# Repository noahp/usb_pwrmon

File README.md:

usb_pwrmon
=====
Simple usb port current/voltage measurement with display.

render
=====

oled breakout
=====

comp info
=====

oled
-----
http://www.aliexpress.com/snapshot/276751791.html
http://rusticengineering.com/2010/05/10/oled-0-96-breakout-board-sh1101a-driver/

micro
-----
freescale ksz24/25/26  
http://cache.freescale.com/files/32bit/doc/data_sheet/KL02P32M48SF0.pdf  
http://cache.freescale.com/files/32bit/doc/ref_manual/KL02P32M48SF0RM.pdf

sns resist:
-----
http://www.mouser.com/ProductDetail/Ohmite/LVK12R010DER/?qs=sGAEpiMZZMtlleCFQhR%2fzSLc77HVEnhv2DNaRf6lglA%3d

opamp:
-----
current sense, fixed at 80 gain:
http://www.mouser.com/ProductDetail/Analog-Devices/AD8293G80ARJZ-R7/?qs=sGAEpiMZZMvEn2pkGav3bNYdL9E%2foSzJYdqf7Uk6kdc%3d
that's a range of 0-4.125A with a shunt resistor of 0.010 Ohms. assuming 16-bit adc (on freescale kl25), ~15 bits per mA.

button:
-----
http://www.mouser.com/Search/ProductDetail.aspx?R=1571621-1virtualkey50660000virtualkey506-1571621-1

usb connectors
-----
[Male A](http://www.mouser.com/ProductDetail/Keystone-Electronics/931/?qs=sGAEpiMZZMulM8LPOQ%252byk63mhAufmuInYp1ViSdVrzg%3d)  
[Female A](http://www.mouser.com/ProductDetail/Amphenol-Commercial-Products/UE27AC5410H/?qs=sGAEpiMZZMulM8LPOQ%252byk4r5VEz1yZV2Iljm%2fKqttNs%3d)  
[Micro B](http://www.mouser.com/ProductDetail/FCI/10118192-0001LF/?qs=sGAEpiMZZMulM8LPOQ%252byk2%252bTbV8%2f2X5vivRX5xKgOBI%3d)

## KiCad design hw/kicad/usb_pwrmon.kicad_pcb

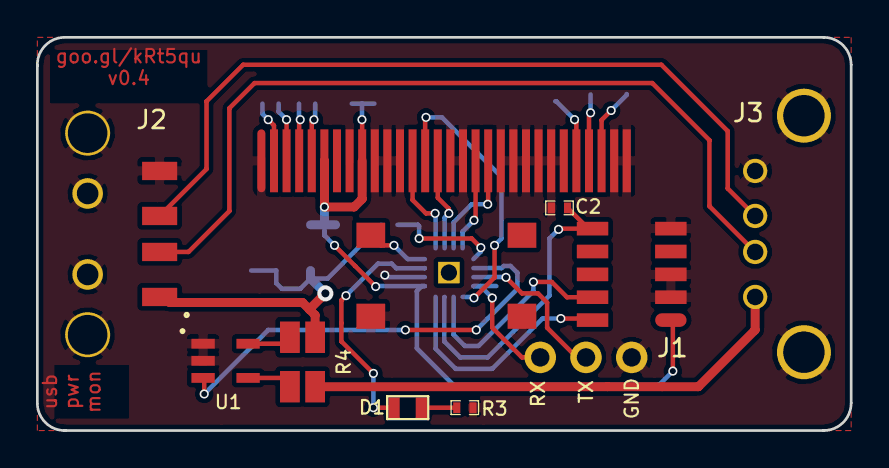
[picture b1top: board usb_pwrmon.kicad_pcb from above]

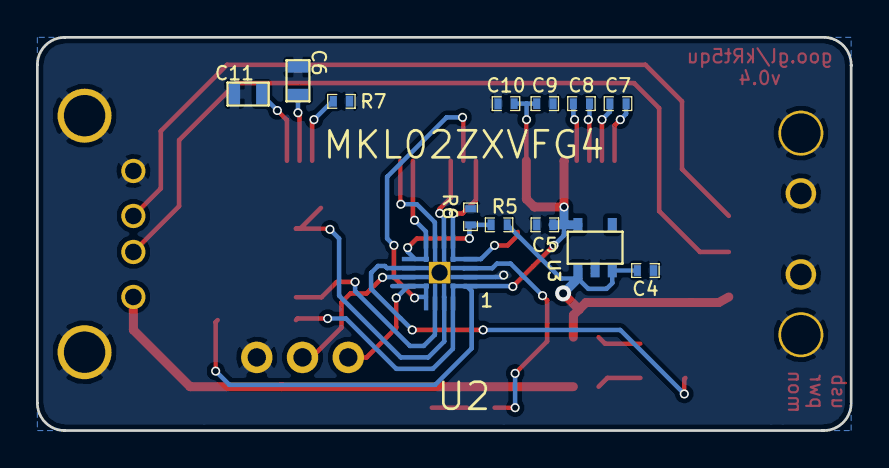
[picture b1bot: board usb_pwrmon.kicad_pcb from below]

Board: 2 copper layers, 45.2 x 21.8 mm, 26 parts (13 on the bottom side), 28 nets.

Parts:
C2: 0.1uF; SM0402
C4, C5, C7, C8, C9, C10: 1uF; SM0402
C6: 2.2uF/16V; SM0603
C11: 10uF; SM0603
D1: LED; SM0603
J1: ARM_10PIN; ARM_10_PIN_SMT
J2: USB_MALE_A; usb_a_male_M701-280442
J3: USB_FEMALE_A; usb_female_a
J_1: OLED_FPC_CONN; oled_fpc_30
P1: TX; TEST_0.100
P2: RX; TEST_0.100
P3: GND; TEST_0.100
R3: 330R; SM0402
R4: LVK12-SHUNT; lvk12
R5, R6: 25K; SM0402
R7: 390K; SM0402
SW1: SW_PUSH; spst_pushbutton_smd
U1: MAX9938; sot23-5_noah
U2: MKL02ZXVFG4; MKL02_QFN16
U3: AAT3221; SOT23-5

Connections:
+3.3v: C5.1, C9.2, C10.2, J1.1, J_1.6, J_1.9, U2.1, U3.5
ADC_OUT: U1.3, U2.10
GND: C2.2, C4.2, C5.2, C6.1, C9.1, C10.1, C11.1, J1.3, J1.5, J1.9, J2.4, J2.5, J3.4, J3.5, J_1.1, J_1.8, J_1.10, J_1.11, J_1.12, J_1.16, J_1.17, J_1.20, J_1.21, J_1.22, J_1.23, J_1.24, J_1.25, J_1.29, J_1.30, P3.1, R3.2, R6.2, R7.1, SW1.1, U1.1, U1.2, U2.2, U3.2
unnamed: D1.2, R3.1
unnamed: D1.1, U2.3
unnamed: J3.1, R4.3, R4.4, U1.4
unnamed: C8.1, J_1.5
unnamed: C7.1, J_1.3
unnamed: C8.2, J_1.4
unnamed: C7.2, J_1.2
unnamed: C11.2, J_1.28
unnamed: C6.2, J_1.27
unnamed: J_1.26, R7.2
NRESET: C2.1, J1.10, U2.15
OLED_D0/SPI_SCLK/I2C_SCK: J_1.18, U2.8
OLED_D1/SPI_SDIN/I2C_SDA: J_1.19, U2.7
OLED_DC/I2X_SA0: J_1.15, U2.6
OLED_~CS: J_1.13, U2.5
OLED_~RST: J_1.14, U2.13
SERIAL_RX: P2.1, U2.12
SERIAL_TX: P1.1, U2.11
SWCLK: J1.4, U2.14
SWDIO: J1.2, U2.16
SW_SNS: SW1.2, U2.4
USB_DM: J2.3, J3.3
USB_DP: J2.2, J3.2
USB_VBUS: C4.1, J2.1, R4.1, R4.2, R5.1, U1.5, U3.1, U3.3
VBUS_SENSE: R5.2, R6.1, U2.9

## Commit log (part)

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2013-01-23 - add basic kicad project & blank schematic
2013-01-23 - add pic & lcd panel components
2013-02-22 - add usb ports (will be m/f footprints later).
2013-02-23 - few more pins.
2013-02-23 - add pushbutton for wakeup (portb) and control
2013-02-23 - add ftdi, add decouples for ic vpp
2013-02-25 - rename usb connectors
2013-03-11 - update to low-side current sense. i think this is about done.
2013-06-25 - add kicadlib submodule
2013-08-04 - add cmp file
2013-08-04 - remove everything except one op-amp
2013-10-09 - add oled display docs
    Former-commit-id: 7fdf5cce20b69188c61fdde9001fc521c2195e7e
2013-10-09 - add oled display docs
2013-10-11 save
2013-10-11 - remove submodule?
2013-10-11 add lib
2013-10-11 remove old format pcb
2013-10-11 pcb renders
2013-10-29 Update README.md
    Former-commit-id: 70bd3ad641af45a11b6eda4deac7096167ec7fa2 [formerly 70bd3ad641af45a11b6eda4deac7096167ec7fa2 [formerly 16fa63f3193e395ecc1da543856f4a60976ed051]]
    Former-commit-id: 736f9969bc4425ab0775a6e428a168e7dd024f6e
    Former-commit-id: 912d237d8af61a4f4f4660b6a735a109fcdfcc66
2013-10-29 Update README.md
    Former-commit-id: 6964e2daf4fc5f64c7605d358488f3e401891eeb
2013-10-29 Update README.md
    Former-commit-id: b29b2106ccbbed165739fa0c228b58bd4ef09a9a
2013-10-30 Update README.md
    Former-commit-id: b8099f7d58f96c51709ed39b64d6d2cdd5e7d5e7 [formerly b8099f7d58f96c51709ed39b64d6d2cdd5e7d5e7 [formerly c15122072ee5d19dd1f13ced2584c3b0514e7588]]
    Former-commit-id: cf23cb98488d09c327cf99636e96615ef90f1e47
    Former-commit-id: be61c741d09226cad19315a5aa11420df0aa2ce2
2013-10-31 remove ref files
    Former-commit-id: 517aac4d8dee8b040f95a6394ec9b84ba33d6f9b
2013-10-31 remove gerbers
    Former-commit-id: 32eedcece8f8c7c22dcb1d825b03550649e028e7
2013-10-31 add old gerbers to subfolder
    Former-commit-id: 506f4019bd9ce86fdc2229ec208849322aa528c9 [formerly 506f4019bd9ce86fdc2229ec208849322aa528c9 [formerly 5891018200ce89c8d6c42409d1824482201694f4]]
    Former-commit-id: d5a737b1643705d074663e591d51fc8108181a90
    Former-commit-id: 41f91e4560a02bc82f3c82b34b4f3513ce68339e
2013-10-31 add old gerbers to subfolder
    Former-commit-id: 5891018200ce89c8d6c42409d1824482201694f4
2013-10-31 update kicadlib
2013-10-31 new schematic with mkl24/5 and ad8293g80 amp
    Former-commit-id: ac4693991d8abdc5d445cbaefc909b446d0d6420 [formerly ac4693991d8abdc5d445cbaefc909b446d0d6420 [formerly 4a9109472a9407fe635b43a95cd1c65a3b81beb9]]
    Former-commit-id: 1dbed20921111c72b593823ada45a3dbf7315b21
    Former-commit-id: 6b7cd41b20ec488c91ded0642a15e9776eb08592
2013-10-31 working on sch
    Former-commit-id: f8ac0ea2000f7e923b448f6217d0ea35cba610c7 [formerly f8ac0ea2000f7e923b448f6217d0ea35cba610c7 [formerly 29f02dbf4e773d56ffa3c3261b2d66c1b951bd1d]]
    Former-commit-id: c5269c944eb81a72d4da92abec835d3a79df764e
    Former-commit-id: 3b6b85954bec87b50fb528209276810c0470e93d
2013-10-31 pop arm debug header
    Former-commit-id: d5df85ed5a434d3ef5b0c7d2dfbc2d922e464fb3 [formerly d5df85ed5a434d3ef5b0c7d2dfbc2d922e464fb3 [formerly f2c820a7cda0a871eab099a68b0b6fad4a23c513]]
    Former-commit-id: 8dfd089300d51ac9194a1659276579516a26efa6
    Former-commit-id: 3cafe83c497ca93ebd9511251291f78c0a64231a
2013-10-31 pop arm debug header
    Former-commit-id: f2c820a7cda0a871eab099a68b0b6fad4a23c513
2013-11-07 Update README.md
    Former-commit-id: 541ae88adf55100f2ead3d13b665923feb6b35fc [formerly 541ae88adf55100f2ead3d13b665923feb6b35fc [formerly 3313f8d4bca9e39602681fdedcab0baa98b72fa6]]
    Former-commit-id: 9264d39825ae36b9c403045ea3fb9e9853812328
    Former-commit-id: 19a171e3758995f70dade9d33aa752f5fdaea0d5
2013-11-09 - fpc connector
    Former-commit-id: 6685d56f5c7f47c431a70211aba2797cf116a25f [formerly 6685d56f5c7f47c431a70211aba2797cf116a25f [formerly 39fcca6794e6a0a2376122315f6af96ae3c01e4f]]
    Former-commit-id: 3bfaab40e79fdfb916e4c6f7b2db3d4696864c31
    Former-commit-id: dbef93559065cb2be07040512478b7806f2621b6
2013-11-10 - add passives and some connections
    Former-commit-id: 0cbe066add0483a1fb74efe12cbe9abbbee8238b [formerly 0cbe066add0483a1fb74efe12cbe9abbbee8238b [formerly 632aac8206b8db47b8f5b2e04e83e7b3be4b6b11]]
    Former-commit-id: a0e75f49b152e5eca435386ea37dbbfa80a0be74
    Former-commit-id: fe0be35bf74c2a8adf19254a67f5b87cb48fbc1c
2013-11-10 - add passives and some connections
    Former-commit-id: 632aac8206b8db47b8f5b2e04e83e7b3be4b6b11
2013-11-10 sch done
    Former-commit-id: 4d012d6b3e56cf83ea9f75bc49d9e1903af969ce
2013-11-10 - start work on pcb
    Former-commit-id: e6562ca754a2c3bdfaa1edcaa4f370bf0480df17
2013-11-13 - some work on pcb
2013-11-13 layout done
2013-11-13 as ordered
    Former-commit-id: 723d12aa2e927baf709e922beb68eb4c6786b970 [formerly 723d12aa2e927baf709e922beb68eb4c6786b970 [formerly 3f4dc9afe7143e35ff6037357ae27188abc31b63]]
    Former-commit-id: a81fd3ca1cf09aa850dd447895322da6a8cd5efa
    Former-commit-id: 210a18c5bd8d0dae89b912255909798f745396fd
2013-11-13 as ordered
2013-11-13 add pcb images
    Former-commit-id: ef8c1a849b213638d83b8e597bf651b582da5368
2013-11-13 Update README.md
    Former-commit-id: 6bb333fa8edbaf539f8ec23fd432706c74fe40d2 [formerly 6bb333fa8edbaf539f8ec23fd432706c74fe40d2 [formerly b79b7d14ea4196a62dc08a7da970db485cdc07cb]]
    Former-commit-id: 224d66cad698622b3b4647620bc1bb31136878eb
    Former-commit-id: 26d84aeabb5884c2f9502a9ee69e6283194ac2bb
2013-11-27 - forgot to add footprint for r1
    Former-commit-id: 6fa6338699d94fe8eb54d1dcac4f5338db877c7e [formerly 6fa6338699d94fe8eb54d1dcac4f5338db877c7e [formerly 8823c0cdd6673d26dffb1b901427ca3f110487d3]]
    Former-commit-id: f6e8cf4ef06b1c32549699c35b10a2e7af572ef4
    Former-commit-id: e190ec155fe0a6c2ccca85e1ced67a6d5495672b
2013-12-10 - add files from https://github.com/noahp/kl2_qfn_breakout
2013-12-10 - break out oled task. working ok, but some spots are flickering on refresh.
    Former-commit-id: 4fd807b14c605efe994bcd909e894b0ec61a71d0
2013-12-11 - fix some maths on the font display
    Former-commit-id: 43f38a7a79f8d09fc3ff691174b222740aaee15a [formerly 43f38a7a79f8d09fc3ff691174b222740aaee15a [formerly a9a17e5aeff2da4bd8c947d958d7f5e33622d333]]
    Former-commit-id: 7d3cdb2b325a709a23d33da27f5e5d3192b3cf9a
    Former-commit-id: 00a1a59bc257ebbc28f50107cd33dbae9b8315d1
2013-12-11 - fix some maths on the font display
2013-12-11 - remove oled files
2013-12-11 - save, new text
2013-12-15 - switch to directly writing to display
    Former-commit-id: 2ae568b376f2bf793c1a391b4b097a8a5f24d22a [formerly 2ae568b376f2bf793c1a391b4b097a8a5f24d22a [formerly ba04e01af288cc37de422668485ad43ebfc5b538]]
    Former-commit-id: ba79cea1265bdc1f2d1a38217144b406e54dc5a9
    Former-commit-id: 2efd151ff7e1b53714c6a369297ca0160b417812
2013-12-17 -add sw directory from branch oled_brkout
    Former-commit-id: 2187a58c0d69b7bc4c6077dc3c91d1d5fb943d0c
2013-12-17 - some improvements
    Former-commit-id: 27a87565a91d43aa10bbe08a8b4b6ddc32170e96
2013-12-17 - some improvements
    Former-commit-id: ebb0311c8f39fa0d760d19f160044e1531e16516 [formerly ebb0311c8f39fa0d760d19f160044e1531e16516 [formerly 27a87565a91d43aa10bbe08a8b4b6ddc32170e96]]
    Former-commit-id: 0e63d3e06818cf8b88b8df754ce5107d7f23719c
    Former-commit-id: 424d5592b582b53c1012ed008707988e0289e715
2013-12-17 - start popping components for full build
    Former-commit-id: 11e02b19504e34a0ad47f6cdf27526b8bbde8a1c
2013-12-17 - new kicadlib
2013-12-17 - most of the sense circuit done
    Former-commit-id: 1431046ee8a343ab8c89428ac98b7c16f5de6213
2013-12-17 - schematic done
    Former-commit-id: 3f9791fe45759391741d9eae500f426ee7afed1c
2013-12-17 - need to tune up some footprints.
    Former-commit-id: 5474b6cb77bcfb95ddc35ca5c43a57529b639cc6 [formerly 5474b6cb77bcfb95ddc35ca5c43a57529b639cc6 [formerly 06e38749f79564db33a77a4455a47758f40de79e]]
    Former-commit-id: e35c6a88c547e092f59bda54ba30af399441276b
    Former-commit-id: cd49700cfbce0e5da90d42b75c5964af1354d0f9
2013-12-17 - need to tune up some footprints.
    Former-commit-id: 06e38749f79564db33a77a4455a47758f40de79e
2013-12-28 -add usb connector parts
    Former-commit-id: 06aa44fea34590f5549b0974a5d55280002f5cbf [formerly 06aa44fea34590f5549b0974a5d55280002f5cbf [formerly 26304e396ba01b4ea01aee32b87bab811e7d6a16]]
    Former-commit-id: f43928af89c2a0dea240e0b76b1d5991d9f4fd7f
    Former-commit-id: 7d14dc9476098b242752e314ca80750262d4a582
2013-12-28 -add new modules for usb connectors
2013-12-28 -start layout
    Former-commit-id: e4f97c397dd27e1a8441daf506eb10bba976db0d
2013-12-28 Update README.md
    Former-commit-id: 925f82080fe1ef5996c5c860f30588722125dc44 [formerly 925f82080fe1ef5996c5c860f30588722125dc44 [formerly 1d3fa31743c6070ba59795b03056288f6680bdea]]
    Former-commit-id: 821431b1aec0d80a976597d4b022243078c82a9a
    Former-commit-id: beb7d4a7c3db27c1effcbff90fe7a06ba3e3ae41
2014-01-12 -add pushbutton switch
    Former-commit-id: 96da23ec3db1ee23974b00762882926ba7f167f4
2014-01-14 - add noahs face
2014-01-14 - add noahs face
    Former-commit-id: 60d871ddb5854753ab009ff1378e3078081a5074 [formerly 60d871ddb5854753ab009ff1378e3078081a5074 [formerly f5829b4f79dceedc0c0517fca3940c1b3bd3271d]]
    Former-commit-id: cebe1b6d488c2b9c69b0380f461027b73728718d
    Former-commit-id: 207a8747697ce41b9bf4f6dcf67d8ba60a4376de
2014-01-14 Update README.md
    Former-commit-id: 70b581fd9a5dfee4949484cd7f7cc6f661f01873
2014-01-14 Update README.md
    Former-commit-id: eeaa685ec8c4c54b8a4b6458559c880b625e7ae8
2014-01-14 - rename sch
2014-01-14 Update README.md
    Former-commit-id: f59eade4bafa150a99a9c92c14704722e1aca08c
2014-01-14 - save the renders
    Former-commit-id: 4006cc5ba3edcb39448f63b17ae13a16c526dc90
2014-01-14 - rename sch
    Former-commit-id: 0fc4d064c1891d1f442bb0b09f824a163551da9d
2014-01-14 - update pcb render pics
    Former-commit-id: c8e5652ab78b94a0ce53fab217b4d64d1ae5368c
2014-02-08 - add add'l usb jumpers - save some pcb work
    Former-commit-id: 4305312ec84a4c15a7d9898fff606bb72ee18eb2
    Former-commit-id: 04b2ca7ae01f3977115ae03f7eda25a8efc5ed7b
    Former-commit-id: 2e574d4f80fddf631c4dad79bdb68b46444f8834
2014-02-08 Update README.md
    Former-commit-id: 63165f7758b38f0c0dd56fb43ae75af5aaaa8acb
    Former-commit-id: 738c4a29a53b982f261031389decfffabf5bf4a0
    Former-commit-id: cf9240d968e7b7160ea4606bf0f1b6e132435d75
2014-02-08 - fix labels for usb dp/dm
    Former-commit-id: 9a6132e0c8394671b9c07c581e160ab25a986f3f
    Former-commit-id: d3e44395799e84ef5012f8b20a545457baf59de4
    Former-commit-id: 0f8721ac38f384b7a2c523019ac0d14e291278d0
2014-02-26 - new kicadlib - switch to kl02, 16-pin qfn - add 3.3v ldo, add test points for uart and vbus
    Former-commit-id: 6b73e37c5a61869ec02b831764a9e1b411b79fdb
    Former-commit-id: b82c953cdf1c4d54c502bd39f04605f08af406fa
    Former-commit-id: 6b15872bd503c5fe5b9b3c20dffebcff974911b6
2014-02-26 - usb female a
    Former-commit-id: ccaaa97b2c43444f2b510b9b8e7ee648d728e36e
    Former-commit-id: 13790abf4edb0d511f94e29df1291fc08081fdf5
    Former-commit-id: 7e421e945e98d3cc00c6549187cdac136bb47274
2014-02-26 Update README.md
    Former-commit-id: 21d1e6d874e0eb8c0aa24d1066d786806ee40a06
    Former-commit-id: 4efb8abc867ebc06e8d6b136ce51ea233246045c
    Former-commit-id: ed9029f18b74dab7d5b831b43b0ed30e8bb5336d
2014-03-27 - layout about 1/2 done
    Former-commit-id: d0cff35ed20b8f19404ca1928e0e4c997e9cc0fb
    Former-commit-id: 4a8e0d8b3233680ff7140ac2bf066568b7e4d971
    Former-commit-id: 2e3a7731e31c3aed773827895a43c1fdf13a017a
2014-03-27 - plot
    Former-commit-id: 86907a5d905e10bdb23a16498cf26c5446daaa5d
    Former-commit-id: 778dc1c6648ee6b37f4dab20ec6f1bb986e78078
    Former-commit-id: ae39f55aec38241b12d9e8e6f26d06ac834c67c2
2014-03-30 - change to mkl26, tested OK on kl2_qfn_breakout
    Former-commit-id: 277698bead96e3aab7a44201b49e4dacd3c1d812
    Former-commit-id: bdccabb1a72b0dea00d905232cf1ce2c8302682c
    Former-commit-id: 6b638fd73a3d40b877bb479ddec53420b6c4a886
2014-04-24 - save new board
2014-05-23 - fix layout with corrected footprint for micro
2014-05-27 - rebuild borad connectivity, regenerate gerbers
2014-06-25 - fix pcb- broken mcu footprint for whatever reason. also change to use goo.gl url shortener, git.io fails for some reason.
2014-10-03 - resort a bit for mkl02z32
2014-10-03 - add mkl02z32 header
2014-10-04 - change spi pin configuration for mkl02
2014-10-16 - add adc init fxn
2014-10-17 - pretty much working now, except no display :-(
